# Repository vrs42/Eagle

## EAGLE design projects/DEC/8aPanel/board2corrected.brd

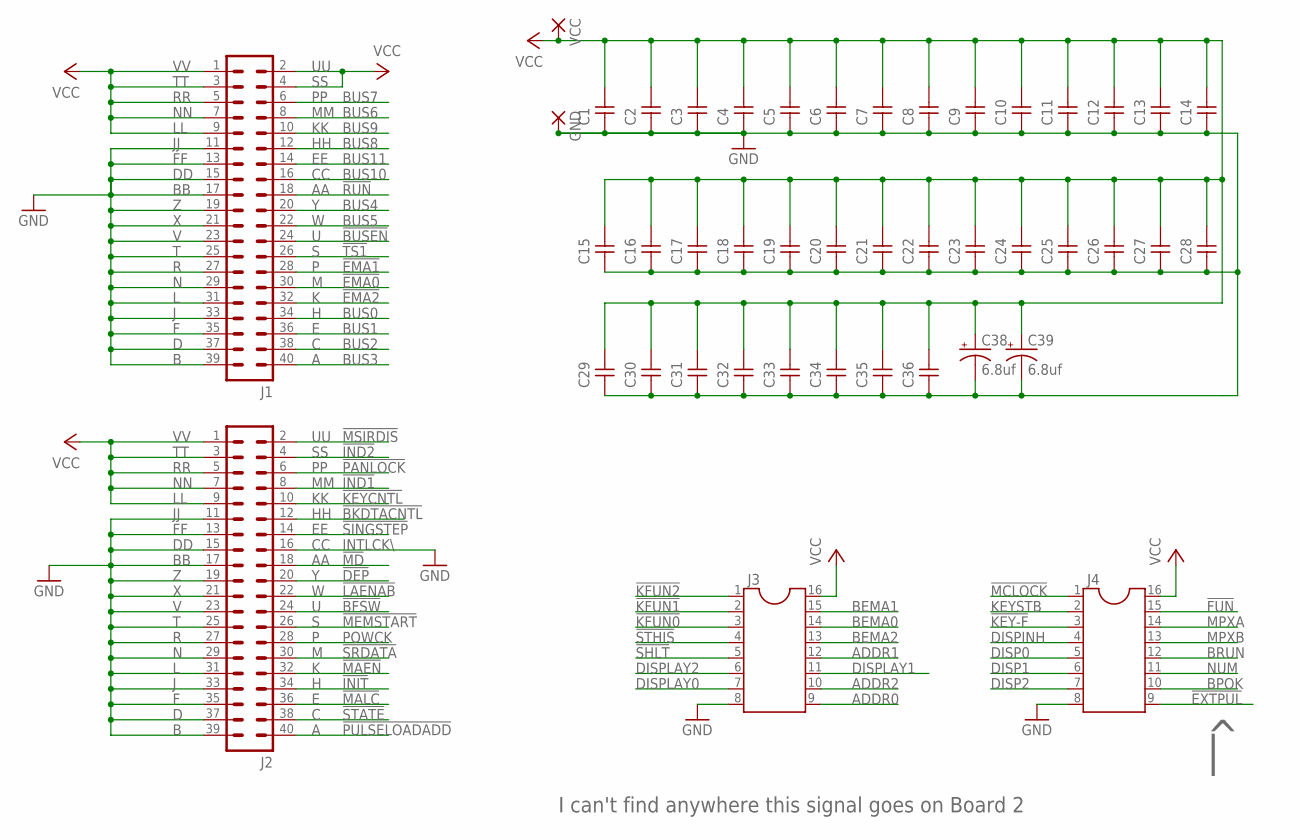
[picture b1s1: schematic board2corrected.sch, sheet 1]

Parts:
C1, C2, C3, C4, C5, C6, C7, C8, C9, C10, C11, C12, C13, C14, C15, C16, C17, C18, C19, C20, C21, C22, C23, C24, C25, C26, C27, C28, C29, C30, C31, C32, C33, C34, C35, C36: CAPNP-5; C-5
C38, C39: 6.8uf; E15-5
GND: 3,81/1,4
J1, J2: 40H
J3, J4: DIL16S; SOCKET-16
VCC: 3,81/1,4

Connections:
!BFSW: J2.24; also elsewhere on the board
!BKDTACNTL: J2.12; also elsewhere on the board
!BUSEN: J1.24; also elsewhere on the board
!DEP: J2.20; also elsewhere on the board
!EMA0: J1.30; also elsewhere on the board
!EMA1: J1.28; also elsewhere on the board
!EMA2: J1.32; also elsewhere on the board
!EXTPUL: J4.9
!FUN: J4.15; also elsewhere on the board
!IND1: J2.8; also elsewhere on the board
!IND2: J2.4; also elsewhere on the board
!INIT: J2.34; also elsewhere on the board
!KEY-F: J4.3; also elsewhere on the board
!KEYCNTL: J2.10; also elsewhere on the board
!KFUN0: J3.3; also elsewhere on the board
!KFUN1: J3.2; also elsewhere on the board
!KFUN2: J3.1; also elsewhere on the board
!LAENAB: J2.22; also elsewhere on the board
!MAEN: J2.32; also elsewhere on the board
!MALC: J2.36; also elsewhere on the board
!MCLOCK: J4.1; also elsewhere on the board
!MD: J2.18; also elsewhere on the board
!MEMSTART: J2.26; also elsewhere on the board
!MSIRDIS: J2.2; also elsewhere on the board
!PANLOCK: J2.6; also elsewhere on the board
!PULSELOADADD: J2.40; also elsewhere on the board
!RUN: J1.18; also elsewhere on the board
!SHLT: J3.5; also elsewhere on the board
!SINGSTEP: J2.14; also elsewhere on the board
!SRDATA: J2.30; also elsewhere on the board
!STATE: J2.38; also elsewhere on the board
!STHIS: J3.4; also elsewhere on the board
!TS1: J1.26; also elsewhere on the board
ADDR0: J3.9; also elsewhere on the board
ADDR1: J3.12; also elsewhere on the board
ADDR2: J3.10; also elsewhere on the board
BEMA0: J3.14; also elsewhere on the board
BEMA1: J3.15; also elsewhere on the board
BEMA2: J3.13; also elsewhere on the board
BPOK: J4.10; also elsewhere on the board
BRUN: J4.12; also elsewhere on the board
BUS0: J1.34; also elsewhere on the board
BUS1: J1.36; also elsewhere on the board
BUS2: J1.38; also elsewhere on the board
BUS3: J1.40; also elsewhere on the board
BUS4: J1.20; also elsewhere on the board
BUS5: J1.22; also elsewhere on the board
BUS6: J1.8; also elsewhere on the board
BUS7: J1.6; also elsewhere on the board
BUS8: J1.12; also elsewhere on the board
BUS9: J1.10; also elsewhere on the board
BUS10: J1.16; also elsewhere on the board
BUS11: J1.14; also elsewhere on the board
DISP0: J4.5; also elsewhere on the board
DISP1: J4.6; also elsewhere on the board
DISP2: J4.7; also elsewhere on the board
DISPINH: J4.4; also elsewhere on the board
DISPLAY0: J3.7; also elsewhere on the board
DISPLAY1: J3.11; also elsewhere on the board
DISPLAY2: J3.6; also elsewhere on the board
GND: C1.1, C2.1, C3.1, C4.1, C5.1, C6.1, C7.1, C8.1, C9.1, C10.1, C11.1, C12.1, C13.1, C14.1, C15.1, C16.1, C17.1, C18.1, C19.1, C20.1, C21.1, C22.1, C23.1, C24.1, C25.1, C26.1, C27.1, C28.1, C29.1, C30.1, C31.1, C32.1, C33.1, C34.1, C35.1, C36.1, C38.-, C39.-, GND.1, J1.11, J1.13, J1.15, J1.17, J1.19, J1.21, J1.23, J1.25, J1.27, J1.29, J1.31, J1.33, J1.35, J1.37, J1.39, J2.11, J2.13, J2.15, J2.16, J2.17, J2.19, J2.21, J2.23, J2.25, J2.27, J2.29, J2.31, J2.33, J2.35, J2.37, J2.39, J3.8, J4.8; also elsewhere on the board
KEYSTB: J4.2; also elsewhere on the board
MPXA: J4.14; also elsewhere on the board
MPXB: J4.13; also elsewhere on the board
NUM: J4.11; also elsewhere on the board
POWCK: J2.28; also elsewhere on the board
VCC: C1.2, C2.2, C3.2, C4.2, C5.2, C6.2, C7.2, C8.2, C9.2, C10.2, C11.2, C12.2, C13.2, C14.2, C15.2, C16.2, C17.2, C18.2, C19.2, C20.2, C21.2, C22.2, C23.2, C24.2, C25.2, C26.2, C27.2, C28.2, C29.2, C30.2, C31.2, C32.2, C33.2, C34.2, C35.2, C36.2, C38.+, C39.+, J1.1, J1.2, J1.3, J1.4, J1.5, J1.7, J1.9, J2.1, J2.3, J2.5, J2.7, J2.9, J3.16, J4.16, VCC.1; also elsewhere on the board

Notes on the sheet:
INTLCK\\
I can't find anywhere this signal goes on Board 2

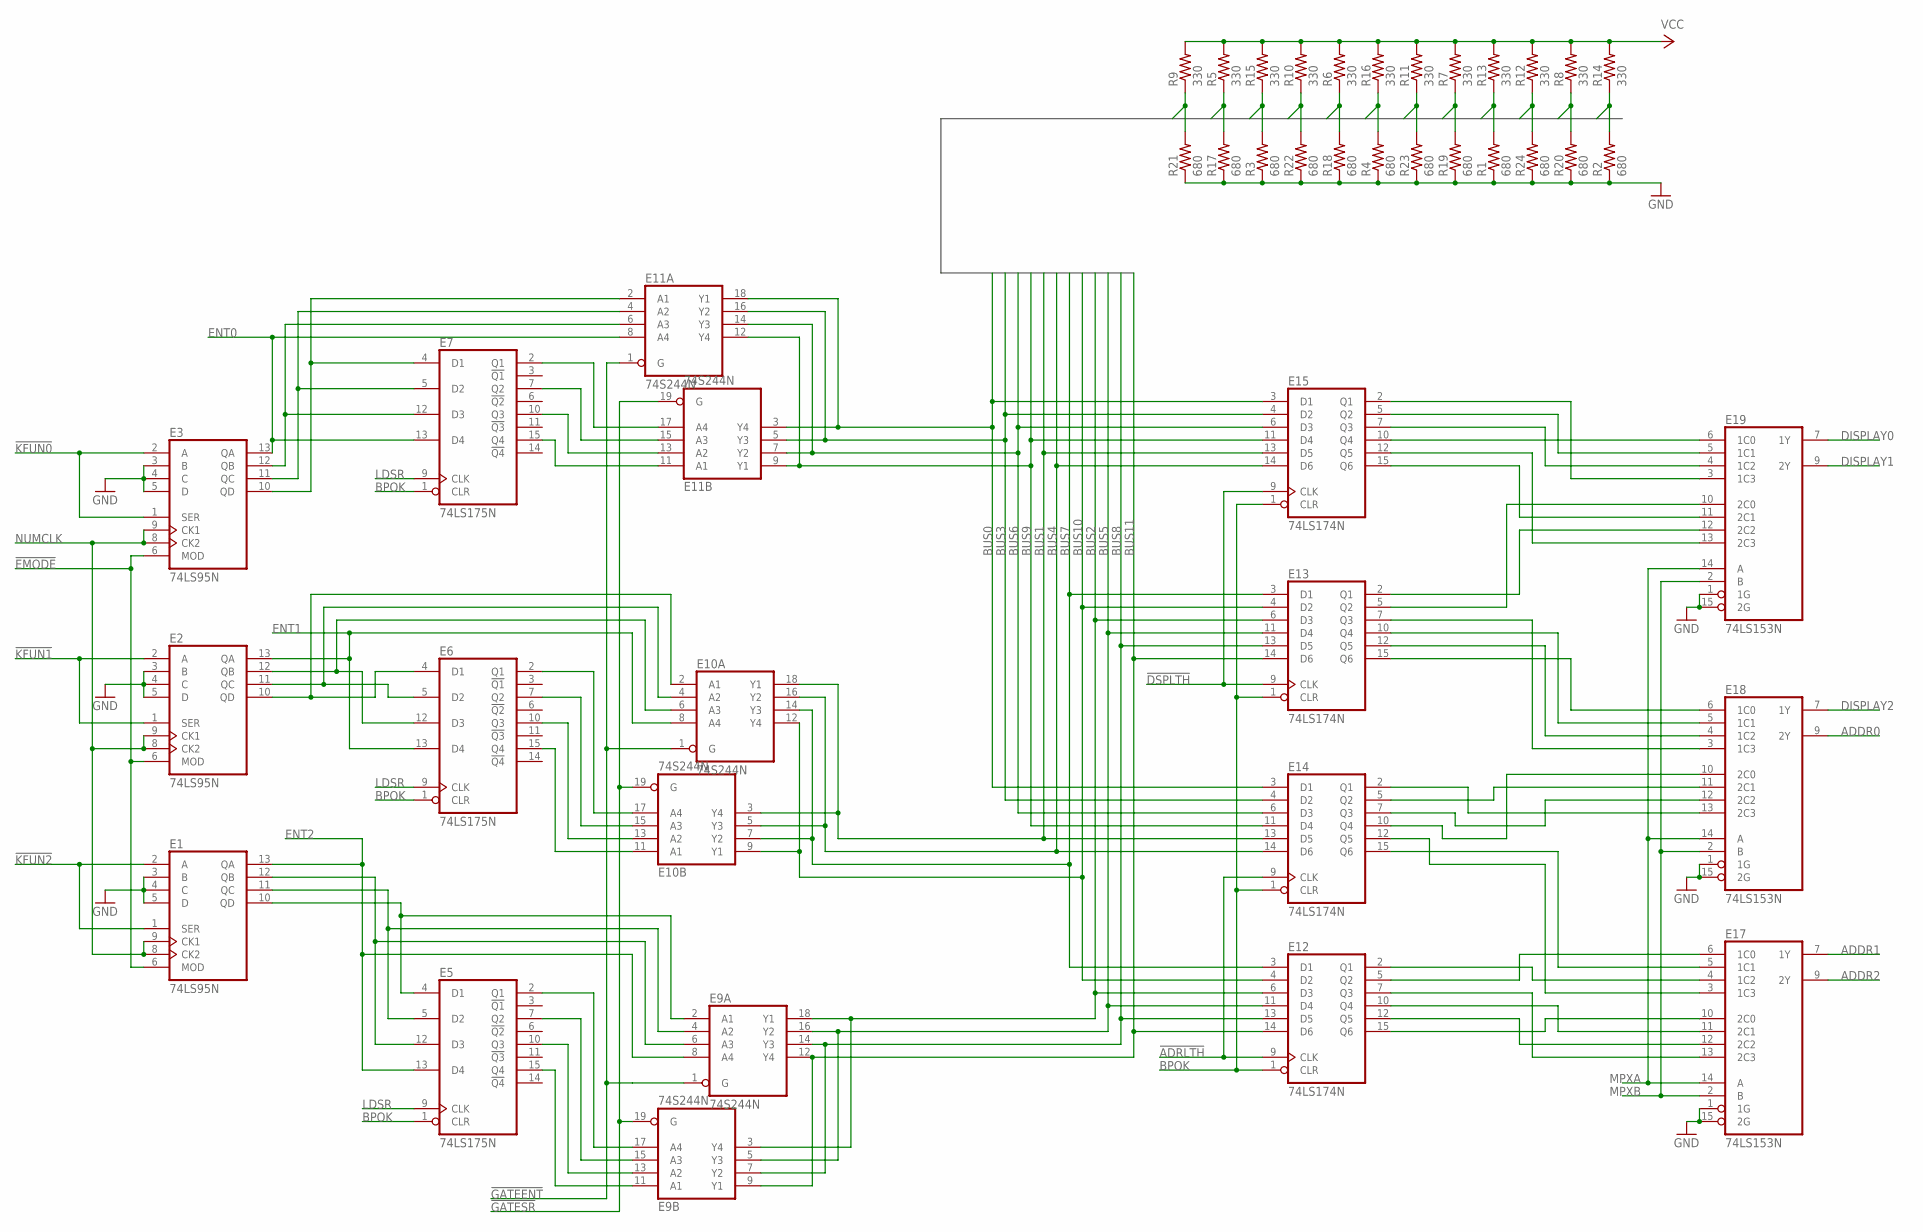
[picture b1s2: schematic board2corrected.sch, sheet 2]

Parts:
E1, E2, E3: 74LS95N; DIL14
E5, E6, E7: 74LS175N; DIL16
E9, E10, E11: 74S244N; DIL20
E12, E13, E14, E15: 74LS174N; DIL16
E17, E18, E19: 74LS153N; DIL16
R1, R2, R3, R4, R17, R18, R19, R20, R21, R22, R23, R24: 680; 0207/10
R5, R6, R7, R8, R9, R10, R11, R12, R13, R14, R15, R16: 330; 0207/10

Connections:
!ADRLTH: E12.9 (CLK), E14.9 (CLK); also elsewhere on the board
!DSPLTH: E13.9 (CLK), E15.9 (CLK); also elsewhere on the board
!EMODE: E1.6 (MOD), E2.6 (MOD), E3.6 (MOD); also elsewhere on the board
!GATEENT: E9.1 (G), E10.1 (G), E11.1 (G); also elsewhere on the board
!GATESR: E9.19 (G), E10.19 (G), E11.19 (G); also elsewhere on the board
!KFUN0: E3.1 (SER), E3.2 (A); also elsewhere on the board
!KFUN1: E2.1 (SER), E2.2 (A); also elsewhere on the board
!KFUN2: E1.1 (SER), E1.2 (A); also elsewhere on the board
ADDR0: E18.9 (2Y); also elsewhere on the board
ADDR1: E17.7 (1Y); also elsewhere on the board
ADDR2: E17.9 (2Y); also elsewhere on the board
BPOK: E5.1 (CLR), E6.1 (CLR), E7.1 (CLR), E12.1 (CLR), E13.1 (CLR), E14.1 (CLR), E15.1 (CLR); also elsewhere on the board
BUS0: E11.3 (Y4), E11.18 (Y1), E14.3 (D1), E15.3 (D1), R9.1, R21.2; also elsewhere on the board
BUS1: E10.3 (Y4), E10.18 (Y1), E14.13 (D5), E15.13 (D5), R5.1, R17.2; also elsewhere on the board
BUS2: E9.3 (Y4), E9.18 (Y1), E12.6 (D3), E13.6 (D3), R3.2, R15.1; also elsewhere on the board
BUS3: E11.5 (Y3), E11.16 (Y2), E14.4 (D2), E15.4 (D2), R10.1, R22.2; also elsewhere on the board
BUS4: E10.5 (Y3), E10.16 (Y2), E14.14 (D6), E15.14 (D6), R6.1, R18.2; also elsewhere on the board
BUS5: E9.5 (Y3), E9.16 (Y2), E12.11 (D4), E13.11 (D4), R4.2, R16.1; also elsewhere on the board
BUS6: E11.7 (Y2), E11.14 (Y3), E14.6 (D3), E15.6 (D3), R11.1, R23.2; also elsewhere on the board
BUS7: E10.7 (Y2), E10.14 (Y3), E12.3 (D1), E13.3 (D1), R7.1, R19.2; also elsewhere on the board
BUS8: E9.7 (Y2), E9.14 (Y3), E12.13 (D5), E13.13 (D5), R1.2, R12.1, R13.1, R24.2; also elsewhere on the board
BUS9: E11.9 (Y1), E11.12 (Y4), E14.11 (D4), E15.11 (D4); also elsewhere on the board
BUS10: E10.9 (Y1), E10.12 (Y4), E12.4 (D2), E13.4 (D2), R8.1, R20.2; also elsewhere on the board
BUS11: E9.9 (Y1), E9.12 (Y4), E12.14 (D6), E13.14 (D6), R2.2, R14.1; also elsewhere on the board
DISPLAY0: E19.7 (1Y); also elsewhere on the board
DISPLAY1: E19.9 (2Y); also elsewhere on the board
DISPLAY2: E18.7 (1Y); also elsewhere on the board
ENT0: E3.13 (QA), E7.13 (D4), E11.8 (A4); also elsewhere on the board
ENT1: E2.13 (QA), E6.13 (D4), E10.8 (A4); also elsewhere on the board
ENT2: E1.13 (QA), E5.13 (D4), E9.8 (A4); also elsewhere on the board
GND: E1.3 (B), E1.4 (C), E1.5 (D), E1.7 (GND), E2.3 (B), E2.4 (C), E2.5 (D), E2.7 (GND), E3.3 (B), E3.4 (C), E3.5 (D), E3.7 (GND), E5.8 (GND), E6.8 (GND), E7.8 (GND), E9.10 (GND), E10.10 (GND), E11.10 (GND), E12.8 (GND), E13.8 (GND), E14.8 (GND), E15.8 (GND), E17.1 (1G), E17.8 (GND), E17.15 (2G), E18.1 (1G), E18.8 (GND), E18.15 (2G), E19.1 (1G), E19.8 (GND), E19.15 (2G), R1.1, R2.1, R3.1, R4.1, R17.1, R18.1, R19.1, R20.1, R21.1, R22.1, R23.1, R24.1; also elsewhere on the board
LDSR: E5.9 (CLK), E6.9 (CLK), E7.9 (CLK); also elsewhere on the board
MPXA: E17.14 (A), E18.14 (A), E19.14 (A); also elsewhere on the board
MPXB: E17.2 (B), E18.2 (B), E19.2 (B); also elsewhere on the board
unnamed: E2.12 (QB), E6.12 (D3), E10.6 (A3)
unnamed: E1.12 (QB), E5.12 (D3), E9.6 (A3)
unnamed: E1.10 (QD), E5.4 (D1), E9.2 (A1)
unnamed: E1.11 (QC), E5.5 (D2), E9.4 (A2)
unnamed: E2.10 (QD), E6.4 (D1), E10.2 (A1)
unnamed: E2.11 (QC), E6.5 (D2), E10.4 (A2)
unnamed: E3.12 (QB), E7.12 (D3), E11.6 (A3)
unnamed: E3.10 (QD), E7.4 (D1), E11.2 (A1)
unnamed: E3.11 (QC), E7.5 (D2), E11.4 (A2)
unnamed: E15.2 (Q1), E19.3 (1C3)
unnamed: E15.5 (Q2), E19.5 (1C1)
unnamed: E15.7 (Q3), E19.4 (1C2)
unnamed: E15.10 (Q4), E19.6 (1C0)
unnamed: E15.12 (Q5), E19.13 (2C3)
unnamed: E15.15 (Q6), E19.11 (2C1)
unnamed: E13.2 (Q1), E19.12 (2C2)
unnamed: E13.5 (Q2), E19.10 (2C0)
unnamed: E13.7 (Q3), E18.3 (1C3)
unnamed: E13.10 (Q4), E18.5 (1C1)
unnamed: E13.12 (Q5), E18.4 (1C2)
unnamed: E13.15 (Q6), E18.6 (1C0)
unnamed: E14.2 (Q1), E18.13 (2C3)
unnamed: E14.5 (Q2), E18.11 (2C1)
unnamed: E14.7 (Q3), E18.12 (2C2)
unnamed: E14.10 (Q4), E18.10 (2C0)
unnamed: E12.15 (Q6), E17.10 (2C0)
unnamed: E12.12 (Q5), E17.12 (2C2)
unnamed: E12.10 (Q4), E17.11 (2C1)
unnamed: E12.7 (Q3), E17.13 (2C3)
unnamed: E14.15 (Q6), E17.5 (1C1)
unnamed: E14.12 (Q5), E17.3 (1C3)
unnamed: E12.2 (Q1), E17.4 (1C2)
unnamed: E12.5 (Q2), E17.6 (1C0)
unnamed: E7.15 (Q4), E11.11 (A1)
unnamed: E7.10 (Q3), E11.13 (A2)
unnamed: E7.7 (Q2), E11.15 (A3)
unnamed: E7.2 (Q1), E11.17 (A4)
unnamed: E6.15 (Q4), E10.11 (A1)
unnamed: E6.10 (Q3), E10.13 (A2)
unnamed: E6.7 (Q2), E10.15 (A3)
unnamed: E6.2 (Q1), E10.17 (A4)
unnamed: E5.15 (Q4), E9.11 (A1)
unnamed: E5.10 (Q3), E9.13 (A2)
unnamed: E5.2 (Q1), E9.17 (A4)
unnamed: E5.7 (Q2), E9.15 (A3)
NUMCLK: E1.8 (CK2), E1.9 (CK1), E2.8 (CK2), E2.9 (CK1), E3.8 (CK2), E3.9 (CK1); also elsewhere on the board
VCC: E1.14 (VCC), E2.14 (VCC), E3.14 (VCC), E5.16 (VCC), E6.16 (VCC), E7.16 (VCC), E9.20 (VCC), E10.20 (VCC), E11.20 (VCC), E12.16 (VCC), E13.16 (VCC), E14.16 (VCC), E15.16 (VCC), E17.16 (VCC), E18.16 (VCC), E19.16 (VCC), R5.2, R6.2, R7.2, R8.2, R9.2, R10.2, R11.2, R12.2, R13.2, R14.2, R15.2, R16.2; also elsewhere on the board

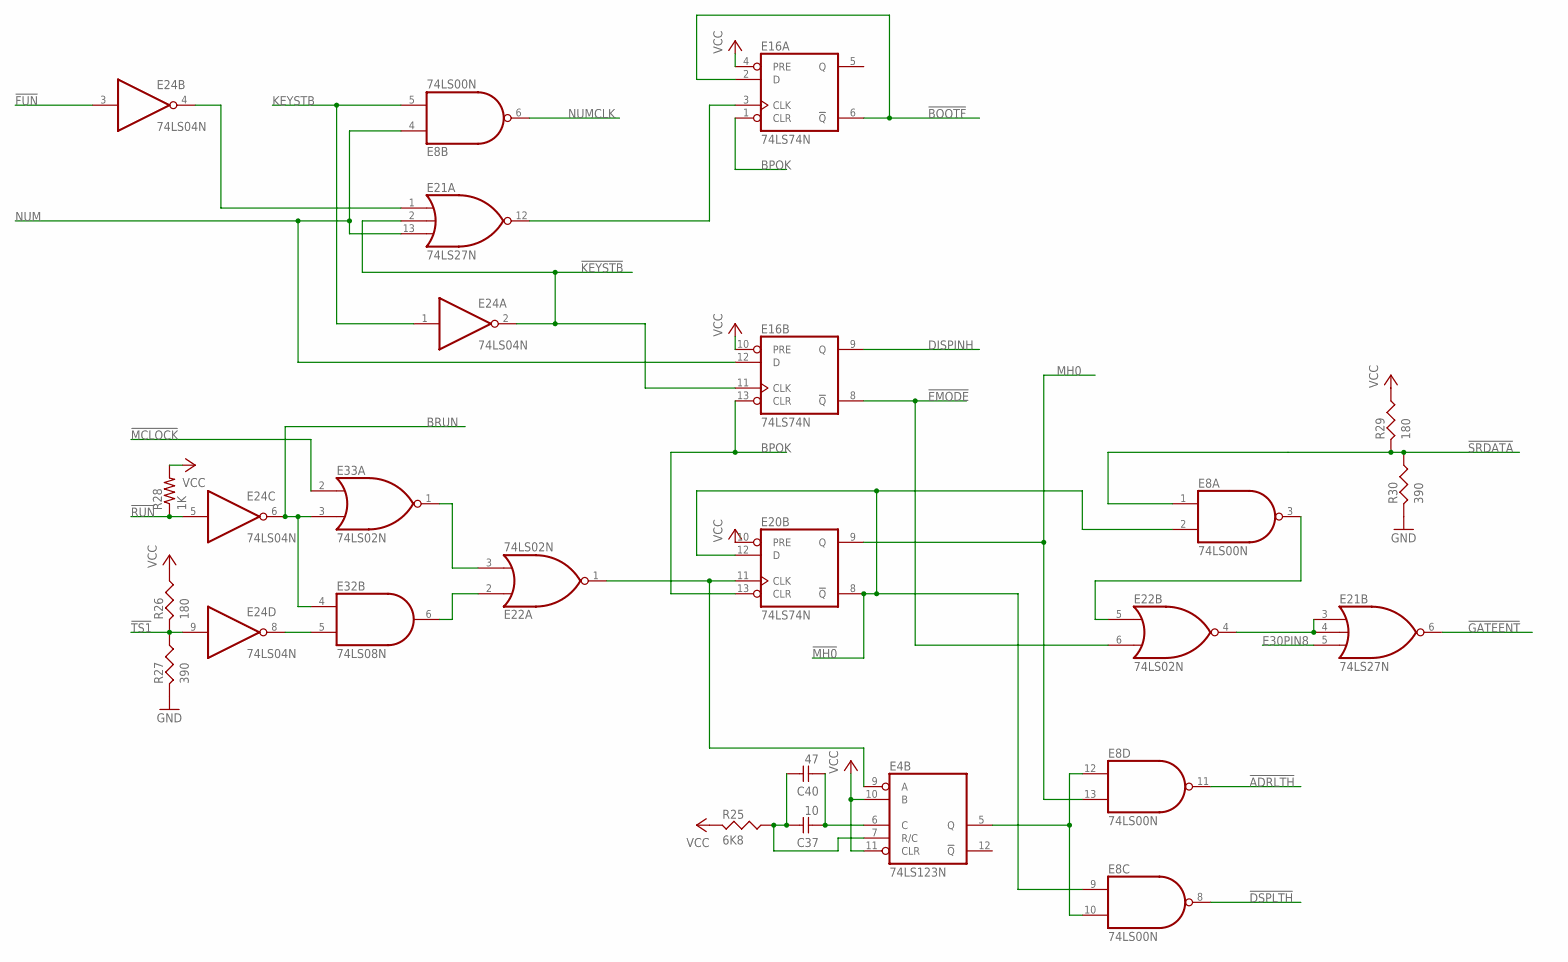
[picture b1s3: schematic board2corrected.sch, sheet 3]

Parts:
C37: 10; C-5
C40: 47; C-5
E4: 74LS123N; DIL16
E8: 74LS00N; DIL14
E16, E20: 74LS74N; DIL14
E21: 74LS27N; DIL14
E22, E33: 74LS02N; DIL14
E24: 74LS04N; DIL14
E32: 74LS08N; DIL14
R25: 6K8; R-10
R26, R29: 180; R-10
R27, R30: 390; R-10
R28: 1K; 0207/10

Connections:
!ADRLTH: E8.11 (O); also elsewhere on the board
!BOOTF: E16.2 (D), E16.6 (!Q); also elsewhere on the board
!DSPLTH: E8.8 (O); also elsewhere on the board
!EMODE: E16.8 (!Q), E22.6 (I1); also elsewhere on the board
!FUN: E24.3 (I); also elsewhere on the board
!GATEENT: E21.6 (O); also elsewhere on the board
!KEYSTB: E16.11 (CLK), E21.2 (I1), E24.2 (O); also elsewhere on the board
!MCLOCK: E33.2 (I0); also elsewhere on the board
!MH0: E8.2 (I1), E8.9 (I0), E20.8 (!Q), E20.12 (D); also elsewhere on the board
!RUN: E24.5 (I), R28.1; also elsewhere on the board
!SRDATA: E8.1 (I0), R29.2, R30.1; also elsewhere on the board
!TS1: E24.9 (I), R26.2, R27.1; also elsewhere on the board
BPOK: E16.1 (CLR), E16.13 (CLR), E20.13 (CLR); also elsewhere on the board
BRUN: E24.6 (O), E32.4 (I0), E33.3 (I1); also elsewhere on the board
DISPINH: E16.9 (Q); also elsewhere on the board
E30PIN8: E21.5 (I2); also elsewhere on the board
GND: E4.8 (GND), E8.7 (GND), E16.7 (GND), E20.7 (GND), E21.7 (GND), E22.7 (GND), E24.7 (GND), E32.7 (GND), E33.7 (GND), R27.2, R30.2; also elsewhere on the board
KEYSTB: E8.5 (I1), E24.1 (I); also elsewhere on the board
MH0: E8.13 (I1), E20.9 (Q); also elsewhere on the board
unnamed: E16.3 (CLK), E21.12 (O)
unnamed: E21.1 (I0), E24.4 (O)
unnamed: E8.3 (O), E22.5 (I0)
unnamed: E22.3 (I1), E33.1 (O)
unnamed: E22.2 (I0), E32.6 (O)
unnamed: E4.9 (A), E20.11 (CLK), E22.1 (O)
unnamed: E24.8 (O), E32.5 (I1)
unnamed: E21.3 (I0), E21.4 (I1), E22.4 (O)
unnamed: E4.5 (Q), E8.10 (I1), E8.12 (I0)
unnamed: C37.1, C40.1, E4.6 (C)
unnamed: C37.2, C40.2, E4.7 (R/C), R25.1
NUM: E8.4 (I0), E16.12 (D), E21.13 (I2); also elsewhere on the board
NUMCLK: E8.6 (O); also elsewhere on the board
VCC: E4.10 (B), E4.11 (CLR), E4.16 (VCC), E8.14 (VCC), E16.4 (PRE), E16.10 (PRE), E16.14 (VCC), E20.10 (PRE), E20.14 (VCC), E21.14 (VCC), E22.14 (VCC), E24.14 (VCC), E32.14 (VCC), E33.14 (VCC), R25.2, R26.1, R28.2, R29.1; also elsewhere on the board

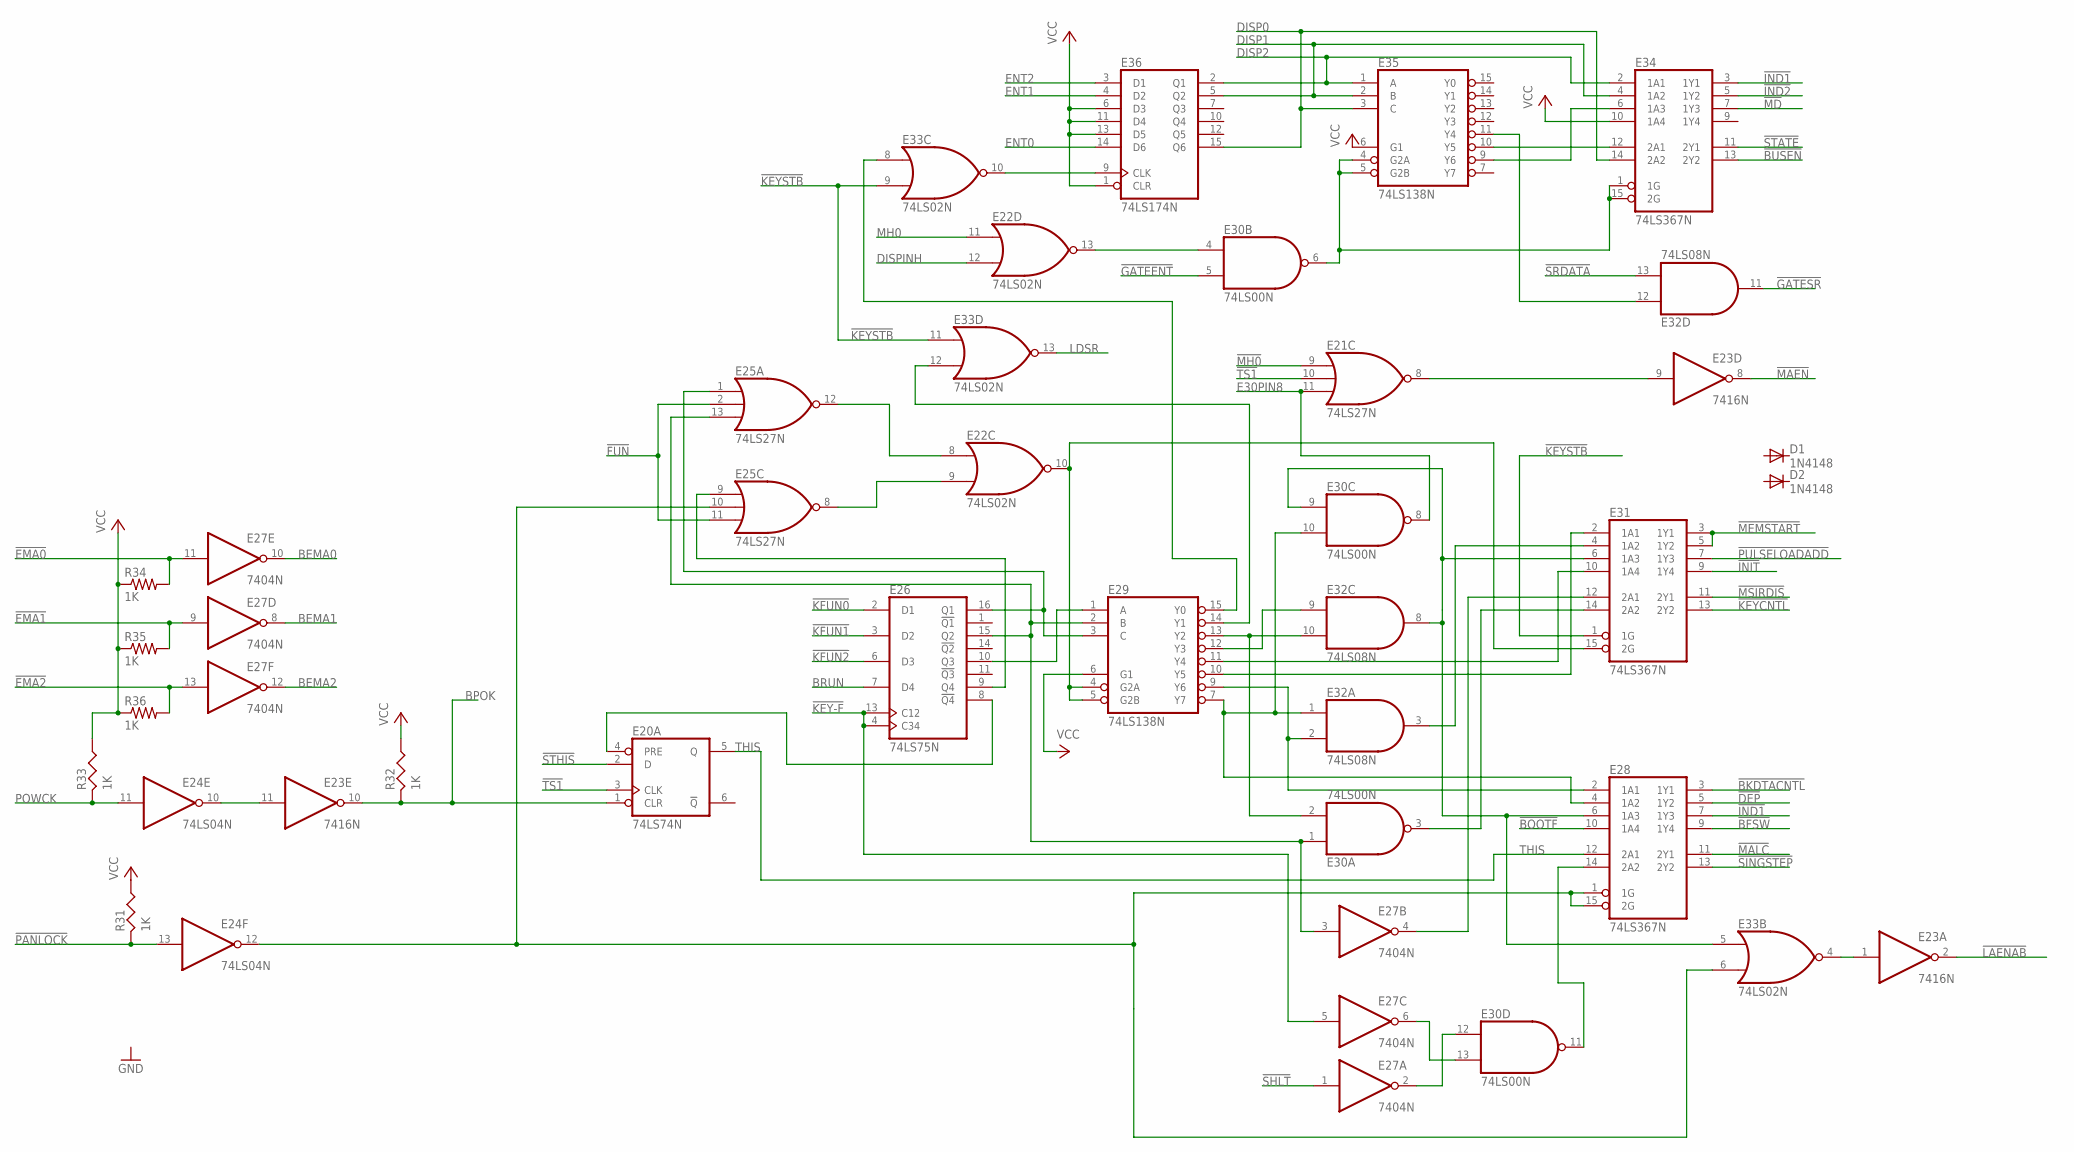
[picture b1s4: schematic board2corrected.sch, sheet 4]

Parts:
D1, D2: 1N4148; DO35-10
E20: 74LS74N; DIL14
E21, E25: 74LS27N; DIL14
E22, E33: 74LS02N; DIL14
E23: 7416N; DIL14
E24: 74LS04N; DIL14
E26: 74LS75N; DIL16
E27: 7404N; DIL14
E28, E31, E34: 74LS367N; DIL16
E29, E35: 74LS138N; DIL16
E30: 74LS00N; DIL14
E32: 74LS08N; DIL14
E36: 74LS174N; DIL16
R31, R32, R33: 1K; R-10
R34, R35, R36: 1K; 0207/10

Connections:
!BFSW: E28.9 (1Y4); also elsewhere on the board
!BKDTACNTL: E28.3 (1Y1); also elsewhere on the board
!BOOTF: E28.10 (1A4); also elsewhere on the board
!BUSEN: E34.13 (2Y2); also elsewhere on the board
!DEP: E28.5 (1Y2); also elsewhere on the board
!EMA0: E27.11 (I), R34.2; also elsewhere on the board
!EMA1: E27.9 (I), R35.2; also elsewhere on the board
!EMA2: E27.13 (I), R36.2; also elsewhere on the board
!FUN: E25.2 (I1), E25.11 (I2); also elsewhere on the board
!GATEENT: E30.5 (I1); also elsewhere on the board
!GATESR: E32.11 (O); also elsewhere on the board
!IND1: E28.7 (1Y3), E34.3 (1Y1); also elsewhere on the board
!IND2: E34.5 (1Y2); also elsewhere on the board
!INIT: E31.9 (1Y4); also elsewhere on the board
!KEY-F: E26.4 (C34), E26.13 (C12), E27.5 (I); also elsewhere on the board
!KEYCNTL: E31.13 (2Y2); also elsewhere on the board
!KEYSTB: E31.1 (1G), E33.9 (I1), E33.11 (I0); also elsewhere on the board
!KFUN0: E26.2 (D1); also elsewhere on the board
!KFUN1: E26.3 (D2); also elsewhere on the board
!KFUN2: E26.6 (D3); also elsewhere on the board
!LAENAB: E23.2 (O); also elsewhere on the board
!MAEN: E23.8 (O); also elsewhere on the board
!MALC: E28.11 (2Y1); also elsewhere on the board
!MD: E34.7 (1Y3); also elsewhere on the board
!MEMSTART: E23.12 (O); also elsewhere on the board
!MH0: E21.9 (I0); also elsewhere on the board
!MSIRDIS: E31.11 (2Y1); also elsewhere on the board
!PANLOCK: E24.13 (I), R31.2; also elsewhere on the board
!PULSELOADADD: E31.7 (1Y3); also elsewhere on the board
!SHLT: E27.1 (I); also elsewhere on the board
!SINGSTEP: E28.13 (2Y2); also elsewhere on the board
!SRDATA: E32.13 (I1); also elsewhere on the board
!STATE: E34.11 (2Y1); also elsewhere on the board
!STHIS: E20.2 (D); also elsewhere on the board
!TS1: E20.3 (CLK), E21.10 (I1); also elsewhere on the board
BEMA0: E27.10 (O); also elsewhere on the board
BEMA1: E27.8 (O); also elsewhere on the board
BEMA2: E27.12 (O); also elsewhere on the board
BPOK: E20.1 (CLR), E23.10 (O), R32.2; also elsewhere on the board
BRUN: E26.7 (D4); also elsewhere on the board
DISP0: E34.14 (2A2), E35.3 (C), E36.15 (Q6); also elsewhere on the board
DISP1: E34.4 (1A2), E35.2 (B), E36.5 (Q2); also elsewhere on the board
DISP2: E34.2 (1A1), E35.1 (A), E36.2 (Q1); also elsewhere on the board
DISPINH: E22.12 (I1); also elsewhere on the board
E30PIN8: E21.11 (I2), E30.8 (O); also elsewhere on the board
E35-Y4: E32.12 (I0), E35.11 (Y4)
ENT0: E36.14 (D6); also elsewhere on the board
ENT1: E36.4 (D2); also elsewhere on the board
ENT2: E36.3 (D1); also elsewhere on the board
GND: E20.7 (GND), E21.7 (GND), E22.7 (GND), E23.7 (GND), E24.7 (GND), E25.7 (GND), E26.12 (GND), E27.7 (GND), E28.8 (GND), E29.8 (GND), E30.7 (GND), E31.8 (GND), E32.7 (GND), E33.7 (GND), E34.8 (GND), E35.8 (GND), E36.8 (GND); also elsewhere on the board
LDSR: E33.13 (O); also elsewhere on the board
MH0: E22.11 (I0); also elsewhere on the board
unnamed: E22.10 (O), E29.4 (G2A), E29.5 (G2B), E31.15 (2G)
unnamed: E22.13 (O), E30.4 (I0)
unnamed: E22.8 (I0), E25.12 (O)
unnamed: E33.10 (O), E36.9 (CLK)
unnamed: E23.11 (I), E24.10 (O)
unnamed: E29.15 (Y0), E33.8 (I0)
unnamed: E26.10 (Q3), E29.1 (A)
unnamed: E25.13 (I2), E26.15 (Q2), E27.3 (I), E29.2 (B), E30.1 (I0)
unnamed: E25.1 (I0), E26.16 (Q1), E29.3 (C)
unnamed: E22.9 (I1), E25.8 (O)
unnamed: D1.A, D2.A, E25.5 (I2)
unnamed: E28.4 (1A2), E29.7 (Y7), E30.10 (I1), E32.1 (I0)
unnamed: E28.2 (1A1), E29.9 (Y6), E32.2 (I1)
unnamed: E29.10 (Y5), E31.2 (1A1)
unnamed: E29.11 (Y4), E31.10 (1A4)
unnamed: E29.12 (Y3), E32.9 (I0)
unnamed: E29.13 (Y2), E30.2 (I1), E32.10 (I1)
unnamed: E29.14 (Y1), E33.12 (I1)
unnamed: E23.1 (I), E33.4 (O)
unnamed: E27.6 (O), E30.13 (I1)
unnamed: E28.14 (2A2), E30.11 (O)
unnamed: E31.4 (1A2), E32.3 (O)
unnamed: E30.6 (O), E34.1 (1G), E34.15 (2G), E35.4 (G2A), E35.5 (G2B)
unnamed: E28.6 (1A3), E30.9 (I0), E31.6 (1A3), E32.8 (O), E33.5 (I0)
unnamed: E34.12 (2A1), E35.10 (Y5)
unnamed: E34.6 (1A3), E35.9 (Y6)
unnamed: E27.4 (O), E31.12 (2A1)
unnamed: E30.3 (O), E31.14 (2A2)
unnamed: E27.2 (O), E30.12 (I0)
unnamed: E23.13 (I), E25.6 (O)
unnamed: E21.8 (O), E23.9 (I)
unnamed: E20.4 (PRE), E26.8 (!Q4)
unnamed: E25.9 (I0), E26.9 (Q4)
PANLOCK: E24.12 (O), E25.10 (I1), E28.1 (1G), E28.15 (2G), E33.6 (I1)
POWCK: E24.11 (I), R33.2; also elsewhere on the board
THIS: E20.5 (Q), E28.12 (2A1)
VCC: E20.14 (VCC), E21.14 (VCC), E22.14 (VCC), E23.14 (VCC), E24.14 (VCC), E25.3 (I0), E25.4 (I1), E25.14 (VCC), E26.5 (VCC), E27.14 (VCC), E28.16 (VCC), E29.6 (G1), E29.16 (VCC), E30.14 (VCC), E31.16 (VCC), E32.14 (VCC), E33.14 (VCC), E34.10 (1A4), E34.16 (VCC), E35.6 (G1), E35.16 (VCC), E36.1 (CLR), E36.6 (D3), E36.11 (D4), E36.13 (D5), E36.16 (VCC), R31.1, R32.1, R33.1, R34.1, R35.1, R36.1; also elsewhere on the board

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
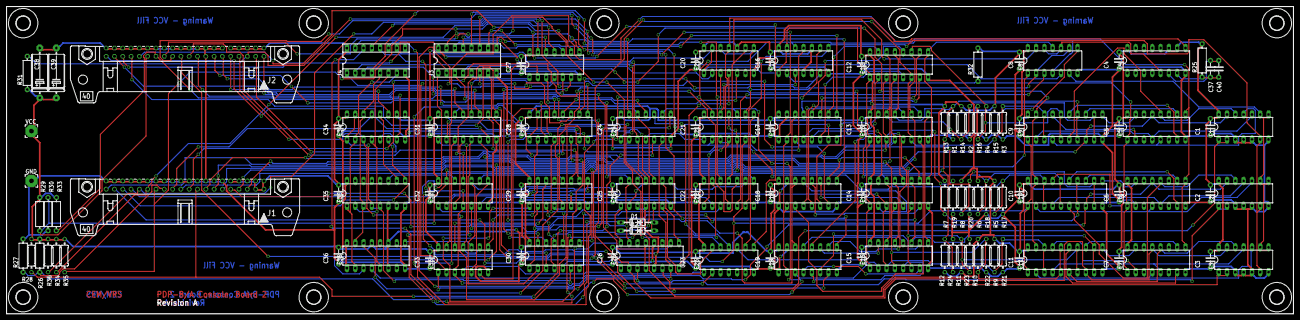
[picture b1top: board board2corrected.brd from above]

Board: 2 copper layers, 393.7 x 94.0 mm, 130 parts (0 on the bottom side), 175 nets.

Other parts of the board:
U$11, U$12, U$13, U$14, U$15, U$16, U$17, U$18, U$19, U$20: 4,3
